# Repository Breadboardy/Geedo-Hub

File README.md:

# Geedo Hub

This is what every Geedo talks to. It serves animations and firmware updates
over the air, and it is where people share what they drew for him.

- **The Hub** — https://breadboardy.github.io/Geedo-Hub/
- **Draw one** — https://breadboardy.github.io/Geedo-Hub/make.html
- **Studio** — https://breadboardy.github.io/Geedo-Hub/studio/
- **Redeem a code** — https://breadboardy.github.io/Geedo-Hub/unlock.html

## How an animation gets on here

1. Draw it in the Studio and press **Publish**. That saves a `.geedo.json`
   and opens the [submission form](https://github.com/Breadboardy/Geedo-Hub/issues/new?template=publish-animation.yml).
2. The bot checks the file the way the robot would (size, speed, the flash
   rule) and posts a preview on the issue. Nothing is published yet.
3. A person looks at it. Every Geedo downloads everything on this list and
   most of the people watching those screens are kids, so nothing goes out
   unseen. A yes is the `approved` label; the bot packs it, lists it with the
   maker's name and the date, signs the manifest and pushes.
4. Every Geedo picks it up at its next check, within the minute.

The hardware design and firmware source are not public.

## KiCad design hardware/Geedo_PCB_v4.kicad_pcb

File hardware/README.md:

# Geedo PCB v4 — repaired (rev 4.3, single-side assembly + power sense)

## Rev 4.3: the board knows its own battery

Four 0402 parts on the back (machine side) give the firmware what rev 4.2
could not: battery voltage and charger status.

- **R10/R11 (100k/100k)**: divider from `/VBAT` to GND; midpoint
  `/VBAT_SENSE` goes to **IO0** (pad 12, ADC1_CH0). 4.2 V reads as 2.1 V,
  inside the ADC's range at 11 dB attenuation. Constant drain is 21 uA -
  about 2.7 years to self-drain a 500 mAh cell, negligible next to the ESP32.
- **C8 (100 nF)**: sampling/filter cap on the divider midpoint.
- **R9 (10k)**: series from the MCP73831's STAT pin (net now named
  `/STAT_RAW`) to **IO1** (pad 13) as `/CHG_STAT`. STAT is tri-state - LOW
  charging, HIGH done, Hi-Z unpowered - the series R prevents contention if
  the pin is ever misconfigured, and `INPUT_PULLUP` makes Hi-Z read HIGH.
- Deliberately NOT on IO2/IO8: those are boot-strapping pins and their
  pull-ups (R8/R2) are load-bearing. STAT driving one low at reset would
  stop the chip booting whenever USB was plugged in.

The schematic gained the same parts, IO0/IO1 pins on the ESP32C3 symbol, and
labels; sch<->pcb verified CONSISTENT. `fab/bom.csv` + `fab/cpl.csv` are
regenerated (19 line items, 29 placements; 100k = LCSC C25741). **If you
exported Gerbers before rev 4.3, re-export** - the old zip has no sense parts.

**Ground pads connect solid, not thermal.** The rev-4.3 sense routing
crowds the corridor under the module, and KiCad's DRC rightly complained
that several GND pads could only get one thermal spoke (it wants two).
Every SMD ground pad now uses a solid zone connection - electrically
better, standard on dense boards, and the parts are machine-reflowed so
the soldering argument for reliefs does not apply. The two through-hole
ground pins (J2/J3) keep their thermal reliefs because those are
hand-soldered.

Checker state after the change: clearance 0, edge 0, keepout 0, courtyards 0,
hole-to-hole 0, nets split 0, GND one pour, netlist CONSISTENT.

## Rev 4.2: one machine-assembled side

Rev 4.1 had SMD parts on both faces, which forces double-sided assembly -
two setups, two stencils, roughly double the labour charge. Rev 4.2 moves
every SMD part to the **back**, so the board qualifies for the cheap
single-side assembly tier:

- **Back (the machine side):** ESP32 module, USB-C, charger, regulator,
  BOOT + RESET buttons, LED, all passives - 22 parts, one paste-place-reflow
  pass. The USB port opens at the board edge as before, just on the back face.
- **Front (the human side):** only what the outside of Geedo touches - the
  OLED socket, the MAIN button, the battery connector, and the silkscreen
  face. All three parts are through-hole: they insert from the front and get
  soldered on the back, the classic TV-remote build. **Zero SMD passes on
  the front.**
- **SW1 stays the original SMD KSC6** (all three buttons are the same part,
  LCSC C221929). It is the one SMD part on the front, so the fab's
  single-side run does NOT place it - **you hand-solder SW1 yourself**: four
  big pads, an easy first SMD joint. For a production run, either pay for
  the second assembly side or swap SW1 to a 6x6 mm THT switch (that variant
  was built and verified in git history, commit c41971e).
- Everything re-routed from scratch (1000+ segments). The old CC2
  board-edge violations are gone - the new route no longer hugs the edge.
- `hardware/fab/bom.csv` and `hardware/fab/cpl.csv` are the assembly-house
  upload files. The LCSC numbers are suggestions - verify stock at order
  time, and expect the fab's reviewer to nudge some rotations; that is
  normal and they confirm before running.
- To revert the whole relayout:
  `cp hardware/Geedo_PCB_v4_BACKUP_two-sided.kicad_pcb hardware/Geedo_PCB_v4.kicad_pcb`

Verified: clearance 0, board-edge 0, keepout 0, courtyards 0, hole-to-hole 0,
all 17 nets single-piece, netlist 29/29 vs schematic, ground one pour with
every pad connected, and all 13 functional circuits (straps, EN reset, USB,
charger, LED, I2C) checked pad-by-pad. Run KiCad DRC with zones filled as the
final authority before ordering.

# Previous: rev 4.1 notes

The v4 design files had schematic symbols with **made-up pin numbers** that did not
match their real-world footprints, so the netlist landed on the wrong physical pads.
As uploaded, the board could not work at all. This revision repairs the netlists in
both the schematic and the board file. **It still needs re-routing in KiCad before
ordering** — see "What you still need to do" below.

## What was broken in v4

| # | Problem | Effect |
|---|---------|--------|
| 1 | Custom ESP32-C3 symbol numbered its pins 1–16 (including GPIOs IO12/IO13 that don't exist on a C3) while the footprint uses the real 53-pad module numbering | 3.3 V power landed on a GND pad, USB data on GND/IO1 pads, chip-enable (EN) on a no-connect pad — the module could never power up or boot |
| 2 | Custom USB-C symbol used pin numbers 1–6; the connector footprint's pads are named A1…B12/S1 | Zero matches → the USB connector was connected to **nothing** (no 5 V in, no data, no charging) |
| 3 | Custom MCP73831 charger symbol numbering wrong (real chip: STAT=1, VSS=2, VBAT=3, VDD=4, PROG=5) | 5 V was wired into the STAT status pin and the chip's actual power pin got the PROG resistor — charger dead |
| 4 | BOOT button on IO8 | ESP32-C3 download mode needs the button on **IO9** (IO8 must stay pulled high); a button on IO8 does nothing useful |
| 5 | IO2 strap pin floating | IO2 must be high at every boot and has no internal pull-up → unreliable/failed boots |
| 6 | Charge LED net floating; R7 shorted the STAT pin to GND | LED could never light |
| 7 | PROG resistor 1 k → commands ~1 A charge current | Double the MCP73831's 500 mA max — chip would overheat |

## What changed in rev 4.1

- `Geedo:ESP32C3` symbol renumbered to the real ESP32-C3-MINI-1 pad map
  (3V3→3, EN→8, IO3→6, IO4→18, IO5→19, IO8→22, USB D−→26/IO18, USB D+→27/IO19),
  plus proper GND pads (1, 2, 11, 14, 36–53, thermal 49_x) and new IO2/IO9 pins.
  Pin *positions* untouched, so the drawing and all existing wires are unchanged.
- `Geedo:USBC` symbol renumbered to real pads: VBUS=A4/B4/A9/B9, D+=A6/B6, D−=A7/B7,
  CC1=A5, CC2=B5, GND=A1/B1/A12/B12 + shield S1.
- `Geedo:MCP73831` renumbered to the real chip (STAT=1, VDD=4, PROG=5).
- Board pad nets rewritten to match all of the above (verified pad-by-pad).
- BOOT button moved to IO9 (`SW2`); the 10 k pull-up `R2` stays on IO8 as required.
- **New parts:** `R8` 10 k pull-up IO2→3V3 (required strap), `C5` 4.7 µF cap on VBUS
  at the charger input. Both are auto-placed — nudge them wherever you like.
- Charge LED rewired as a proper chain: 3V3 → D1 → R7 → STAT pin.
- `R6` (PROG) changed 1 k → **4.7 k** ≈ 215 mA charge current (safe for ≥350 mAh LiPo;
  use 10 k for ~100 mA if the battery is small).
- Removed 140 track segments/vias that were routed to the wrong physical pads.
  Power routing in the charger corner and the GND zones were kept.

## Routing status: bare board, ready to autoroute

All old copper was removed (it was routed to the wrong pads), so the board now has
footprints, nets, and GND zones but **zero tracks**. Net classes are preset so an
autorouter picks up sensible widths automatically:

| Class | Nets | Track width |
|-------|------|-------------|
| Power | GND, +3V3, /VBAT, /VBUS | 0.50 mm |
| USB | /USB_DP, /USB_DN | 0.30 mm |
| Default | everything else | 0.25 mm |

### Steps

Routing runs entirely from the terminal — no KiCad window needed:

```bash
./tools/route_pcb.sh          # export DSN -> Freerouting -> import SES -> save board
./tools/route_pcb.sh 500      # more optimisation passes
```

The script uses KiCad's own Python bindings (`ExportSpecctraDSN` /
`ImportSpecctraSES`, both headless-capable in KiCad 8+), so it needs the system
python that ships with KiCad — not a conda/venv python. It auto-skips any
Freerouting jar too new for the installed Java (2.2.x needs Java 25; the 1.9.0
build runs on Java 11+).

Afterwards:

1. **Check the USB pair by hand.** D+ and D− (J1 A6/B6 → U3 pad 27, A7/B7 → pad 26)
   should run short and side-by-side. If the autorouter sent them on separate
   scenic routes, delete those two tracks and drag them manually — the connector
   sits right next to the module, so it's a quick fix.
2. `kicad-cli pcb drc --schematic-parity hardware/Geedo_PCB_v4.kicad_pcb`
3. Open the board, press `B` to refill zones, and commit if DRC is clean.
4. **Schematic → ERC** once: one known warning, U1 pin "TEMP" has no pad — the
   5-pin MCP73831 has no TEMP pin; delete that symbol pin and its stub wire.

### Layout notes

- Front side: USB-C, ESP32 module, the three buttons, OLED header.
  Back side: charger, regulator, battery connector, all passives. Parts that look
  stacked in 2D (U1 under SW3, U2 under SW2) are on opposite faces — that's fine.
- `R8` sits at the top of the back-side pull-up column with R1/R2/R3;
  `C5` sits just below the charger U1. Both were auto-added in rev 4.1 — move them
  if you prefer, they have no mechanical constraint.

### Firmware pin map after this fix

MAIN button = GPIO3, BOOT/recovery = **GPIO9** (was 8 — update the sketch if it
read GPIO8), I2C `Wire.begin(4, 5)` (SDA=4, SCL=5). USB is native, no pin setup.
Flashing over USB now works normally; hold BOOT while pressing RESET only for recovery.

## Regulator: MCP1826S, not AMS1117 (changed in this revision)

`U2` was an AMS1117-3.3, which needs ~1.1 V more on its input than it puts out.
Fed from a LiPo that is the wrong way round:

| battery | AMS1117 output | MCP1826S output |
|---------|----------------|-----------------|
| 4.2 V (full) | 3.3 V | 3.3 V |
| 3.9 V (~70%) | ~3.2 V, sagging | 3.3 V |
| 3.7 V (nominal) | ~3.0 V, at the chip's minimum | 3.3 V |
| 3.5 V (~20%) | ~2.8 V, brownout | 3.3 V |

WiFi makes it worse exactly when it matters: an ESP32-C3 pulls 300-400 mA in
transmit bursts, which widens the dropout. The board would have run fine after
a charge and then reset during WiFi activity at half battery, losing most of
the pack's usable capacity.

The MCP1826S-3302 drops only 0.25 V, holds 3.3 V down to about 3.55 V of
battery, and keeps the same SOT-223 footprint. It is **not** pin-compatible -
AMS1117 is GND/Vout/Vin with the tab on Vout, MCP1826S is Vin/GND/Vout with the
tab on GND - so U2's pads were remapped and the three nets re-routed. The
schematic symbol was renumbered rather than redrawn, so the existing wiring is
unchanged. Tab-to-ground is also better thermally, since it bonds to the pour.

`C6` (1 uF, back side) was added as a local output capacitor for regulator
stability; C2's 10 uF is 9 mm away on the same net. It sits at (110.30, 115.80),
3 mm from U2's output pin, with 3.3 V routed to U2.3 in four segments that jog
around the VBAT via. It was originally placed 2 mm from the output pin on the
*wrong side* of it, which put it underneath U2's SOT-223 body - not assemblable,
and KiCad was right to flag the courtyard overlap.

`C7` (1 uF, back side, directly under the module's EN pad) was added between EN
and ground. Espressif's guidelines call for this RC with the 10 k pull-up: it
holds reset low while the rail rises, so the chip starts cleanly on a slow
power-up. Without it a board usually boots but can occasionally hang until
reset is pressed.

## Powering the board

The 3.3 V rail is generated from the **battery**. USB 5 V reaches only the
charger, so with no cell installed the MCP73831 has to act as the supply:
it is current-limited to 215 mA and can cycle when the load is light.

- **Flashing with a battery connected:** reliable. Native USB, no serial chip.
- **Flashing with no battery:** usually works (download mode draws well under
  the limit) but the rail is unregulated-ish and a brownout mid-write is
  possible. Nothing is damaged; just retry.
- **Running WiFi with no battery:** will brown out on transmit bursts.

Feeding the regulator from USB *or* battery would fix this properly and is the
main remaining item for rev 5.

## Ground plane: SW2's ground was floating

The copper pour on the front side is split by the CC2 track that runs down
the right-hand side of the board. The strip east of it (roughly x 114-118.5,
y 105-126) carries **SW2's two ground pads** and had no via anywhere on it,
so the BOOT button's ground return was connected to nothing. Two stitching
vias at (118.0, 120.9) and (118.0, 117.4) tie that strip down to the back-side
plane. Ground now resolves to a single 2042 mm2 piece across both layers.

This is what the long-standing "Zone [GND] on F.Cu / Zone [GND] on B.Cu -
unconnected" DRC item was pointing at. It went unexplained for a while because
the offline checking scripts modelled SW2's pads with their width and height
swapped, which painted false copper straight across the gap.

## The antenna keepout was thrown off the board by the flip

Spotted by eye in KiCad: the ESP32's antenna keepout rectangle was drawn far
off to the left of the board, nowhere near the module.

`ESP32-C3-MINI-1` carries three keepout zones nested inside its footprint,
covering the antenna end of the module. **Zones nested in a footprint store
absolute board coordinates**, unlike pads, lines and polygons, which are
footprint-local. The rev-4.2 flip negated every local x, so it turned the
keepout's `x 90.575..103.775` into `-103.775..-90.575` — mirrored about x=0
instead of about the footprint origin, landing ~190 mm off the board.

Nothing flagged it. KiCad's DRC has no rule for "antenna is missing its
keepout", and the board is saved unfilled, so the damage only appears at
**Edit → Fill Zones** — the step right before Gerber export. Simulating the
pour on the pre-fix file shows the ground plane flooding the antenna window
almost completely: 71.2 mm2 on F.Cu and 70.5 mm2 on B.Cu, out of 71.3 mm2.
Solid copper on both sides of a printed antenna detunes it and shorts out its
near field, so the radio would have been crippled on every board in the order.

The fix restores `x 90.575..103.775`. The rectangle is centred on U3's origin
(x = 97.175), so mirroring maps it onto itself — a flipped module needs the
exact same absolute keepout as an unflipped one. After the fix the pour is
kept out entirely (0.65 mm2 residual per layer, which is one 0.05 mm grid row
at the window edge — a rasteriser artifact, not copper).

`tools/flip_footprint.py` carried the same latent bug and would have repeated
it on any future flip. It now holds nested zones out of the local-coordinate
rewrite and mirrors them about the footprint origin with exact decimal
arithmetic, guarded by a new self-test **T5** (zone vertices must land at
`2*fx - x`, alongside T2 for pads). Cross-check: re-flipping U3 from the
two-sided backup with the repaired tool reproduces the corrected coordinates
exactly.

## The 3.3 V rail was in two halves

Caught by KiCad's DRC, not by me. `+3V3` was split into two electrically
separate islands with nothing joining them:

| island | what was on it |
|--------|----------------|
| A | U3.3 (ESP32 3.3 V), U2.3 (regulator output), C6.1, D1.2 |
| B | **J3.2 (OLED 3.3 V)**, R1.1, R2.1, R3.1, R8.1, C2.1, C3.1, C4.1 |

So the regulator's output never reached the OLED header or **any** of the
pull-ups - including the IO2 and IO8 strapping resistors the ESP32-C3 needs
held high to boot, and the IO9 pull-up. The board would not have started.

The routing had got within 1.2 mm of finishing and stopped: a front-side stub
dead-ended at (103.15, 77.85) and a back-side track dead-ended at
(103.96, 77.00), on opposite layers with no via between them. Fixed with a via
at the front-side tip and a 0.5 mm back-side track joining the two.

KiCad reported this as a single "unconnected items" entry, which badly
undersells it - one missing connection was the whole upper half of the rail.
Every net is now checked island-by-island, not just pad-to-pad; see
`tools/drc_offline.py`.

## The logo, and why it never printed

The face logo was a KiCad **reference image** - an `(image ...)` element with a
1254x1254 PNG embedded as base64. Reference images are editor-only: they exist
to trace over and line things up, and KiCad **never plots them to Gerbers**. The
fab had never seen it, on any board.

It was also far too small to print. The PNG is 96% whitespace padding, so at the
stored scale the actual face came out 2.3 mm wide with 0.18 mm strokes - right at
the silkscreen minimum, patchy at best even if it had plotted.

It is now real artwork: the bitmap is traced into outlines and stored as a
footprint, `Geedo:Logo`, of `fp_poly` shapes on **F.SilkS**, which does plot.
Sits at (115.5, 77.5), sized so the face is 6 mm wide with 0.47 mm strokes,
0.90 mm inside the top edge and 1.16 mm from the nearest pad. The mouth's enclosed hole is preserved by fracturing - the hole
is joined to its outer contour by a zero-width slit, which is exactly what
KiCad's own bitmap converter does.

The reference image was removed: it plotted nothing, it sat directly on top of
the new artwork in the editor, and it was 912 kB of base64 in a 1.1 MB board
file (now 205 kB). The source bitmap is kept as `hardware/geedo-logo.png`.

To move or resize it, drag the `LOGO1` footprint in KiCad like any other. To put
it in **copper** instead of silkscreen - bare copper reads gold on ENIG and looks
sharper than white ink - change the `fp_poly` layers to `F.Cu`; it would then
need clearance from the ground pour, so re-run `tools/drc_offline.py` after.

The `Geedo` copper text on the back has been **deleted**. It had been moved once,
from (118.5, 81) to (112.55, 87.3), because a 3.3 V track ran straight through the
lettering - KiCad flagged that as a 0.000 mm clearance violation - but the board
carries its name in the silkscreen logo now, so the copper lettering is gone. That
also means there is no unconnected copper island sitting in the ground pour.

## Check your OLED module's pin order before plugging it in

The header `J3` is wired, physically, as:

| pin | net |
|-----|-----|
| 1 (square pad) | GND |
| 2 | 3V3 |
| 3 | SCL |
| 4 | SDA |

**Checked: the module in use is GND-first, so it matches and plugs straight in.**

Worth knowing if you ever swap displays: some SSD1306 breakouts are ordered
VCC, GND, SCL, SDA instead. Plugging one of those straight in puts 3.3 V on its
ground pin and ground on its supply, which destroys it. Compare the silkscreen
on any new module against the table above first; if it does not match, swap the
two power wires. The board is not wrong, both module variants simply exist.

The schematic used to disagree with this. Its `Conn4` symbol named the pins
VCC, GND, SDA, SCL - both pairs the wrong way round from how the wires actually
run. The wiring and the board were always self-consistent; only the names on the
symbol were wrong, so anyone reading the schematic would have got it backwards.
The pin names now match reality.

Ten other pin labels were stale in the same way, left behind when the symbols
were renumbered. `U2` was still carrying **AMS1117** pin names (`VI`, `VO`,
`GND_Adj`) although it is an MCP1826S, and `U1`'s labels were one position out.
All nets were correct throughout - these were names only - but they are now
corrected so the board reads truthfully in KiCad.

## Not done, if you want them later

- **No reference designators are printed.** 25 of the 26 are hidden, so the
  board gets component outlines and polarity marks but no `R1`/`C2`/`U3` text.
  With four different values across eight identical-looking 0402 resistors,
  hand-populating this means counting positions off the layout. Un-hiding them
  is possible but not automatic: several sit 15-36 mm from their own part, so
  they would need repositioning, and four would land on pads.
- **No pull-ups on SDA/SCL.** I2C needs them. Most SSD1306 modules have their
  own on board, in which case this is fine; if yours does not, the bus will not
  work at all. Two 0402 resistors, 4.7 k, from SDA and SCL to 3V3 would settle it.

## Remaining DRC items

After the last pass KiCad reports **0 unconnected pads**. What is left:

| item | severity | why it stays |
|------|----------|--------------|
| 3x `copper_edge_clearance` on the CC2 trace, 0.348 mm vs 0.5 mm | error | Genuinely unfixable in this layout - see the rev 5 note below. Fabs build 0.35 mm to the outline routinely. |
| `lib_footprint_mismatch` on U3 | warning | The ESP32 module footprint is custom and edited, so it will always differ from the library copy. No effect on fabrication. |

The logo footprint lives in `hardware/Geedo.pretty/`, registered by
`hardware/fp-lib-table`, so `Geedo:Logo` resolves instead of reporting a
missing library.

C5 and C7 previously reported `lib_footprint_mismatch` too. They sat at
rotation 0 while their pads carried an absolute angle of 180, which KiCad reads
as differing from the library. The pads are symmetric roundrects so the two are
the same shape - normalising the angle is bookkeeping, not a geometry change.

## Checking the board without opening KiCad

Two scripts check the board straight from the `.kicad_pcb` file, so they work
on a machine with no KiCad installed and they do not care whether the zones
happen to be filled. Run both from the repo root:

```bash
python3 tools/drc_offline.py    # clearance, board edge, keepout
python3 tools/pour_sim.py       # re-derives the pour, checks GND is one net
```

`pour_sim.py` needs numpy and scipy. It does not read the stored
`filled_polygon` blocks - those go stale the moment anything is re-routed.
It rebuilds the fill from the zone rules instead (clearance, min thickness,
keepouts, edge clearance, island removal), then merges the two layers at
through-hole pads and vias and flood-fills. That is what caught SW2's
floating ground island.

Expected output as of this revision: 0 clearance, 0 keepout, 4 board-edge
(the CC2 trace described below), and ground resolving to a single group with
every ground pad on poured copper. Courtyard overlaps: 0. Nets split across
islands: 0.

These are a second opinion, not a replacement for KiCad's DRC - they do not
model solder-mask bridging, starved thermals or footprint-library parity.
Run `kicad-cli pcb drc --schematic-parity hardware/Geedo_PCB_v4.kicad_pcb`
before ordering, with the zones filled.

## Known caveats to fix in rev 5

- No ESD protection on the USB data lines (add a USBLC6-2SC6 next to J1).
- The CC2 trace runs 0.35 mm from the bottom board edge where the setup asks
  0.5 mm. This one cannot be fixed by moving the trace: it threads the gap
  between SW2's lower pad and the board outline, which is 0.8 mm wide, and
  clearing the pad by 0.2 mm plus the edge by 0.5 mm needs 0.95 mm. Lifting it
  just trades an edge violation for a 0.025 mm pad clearance, which is far
  worse. Fixing it properly means nudging SW2 up a millimetre in rev 5. Most
  fabs build 0.35 mm to the outline without comment.

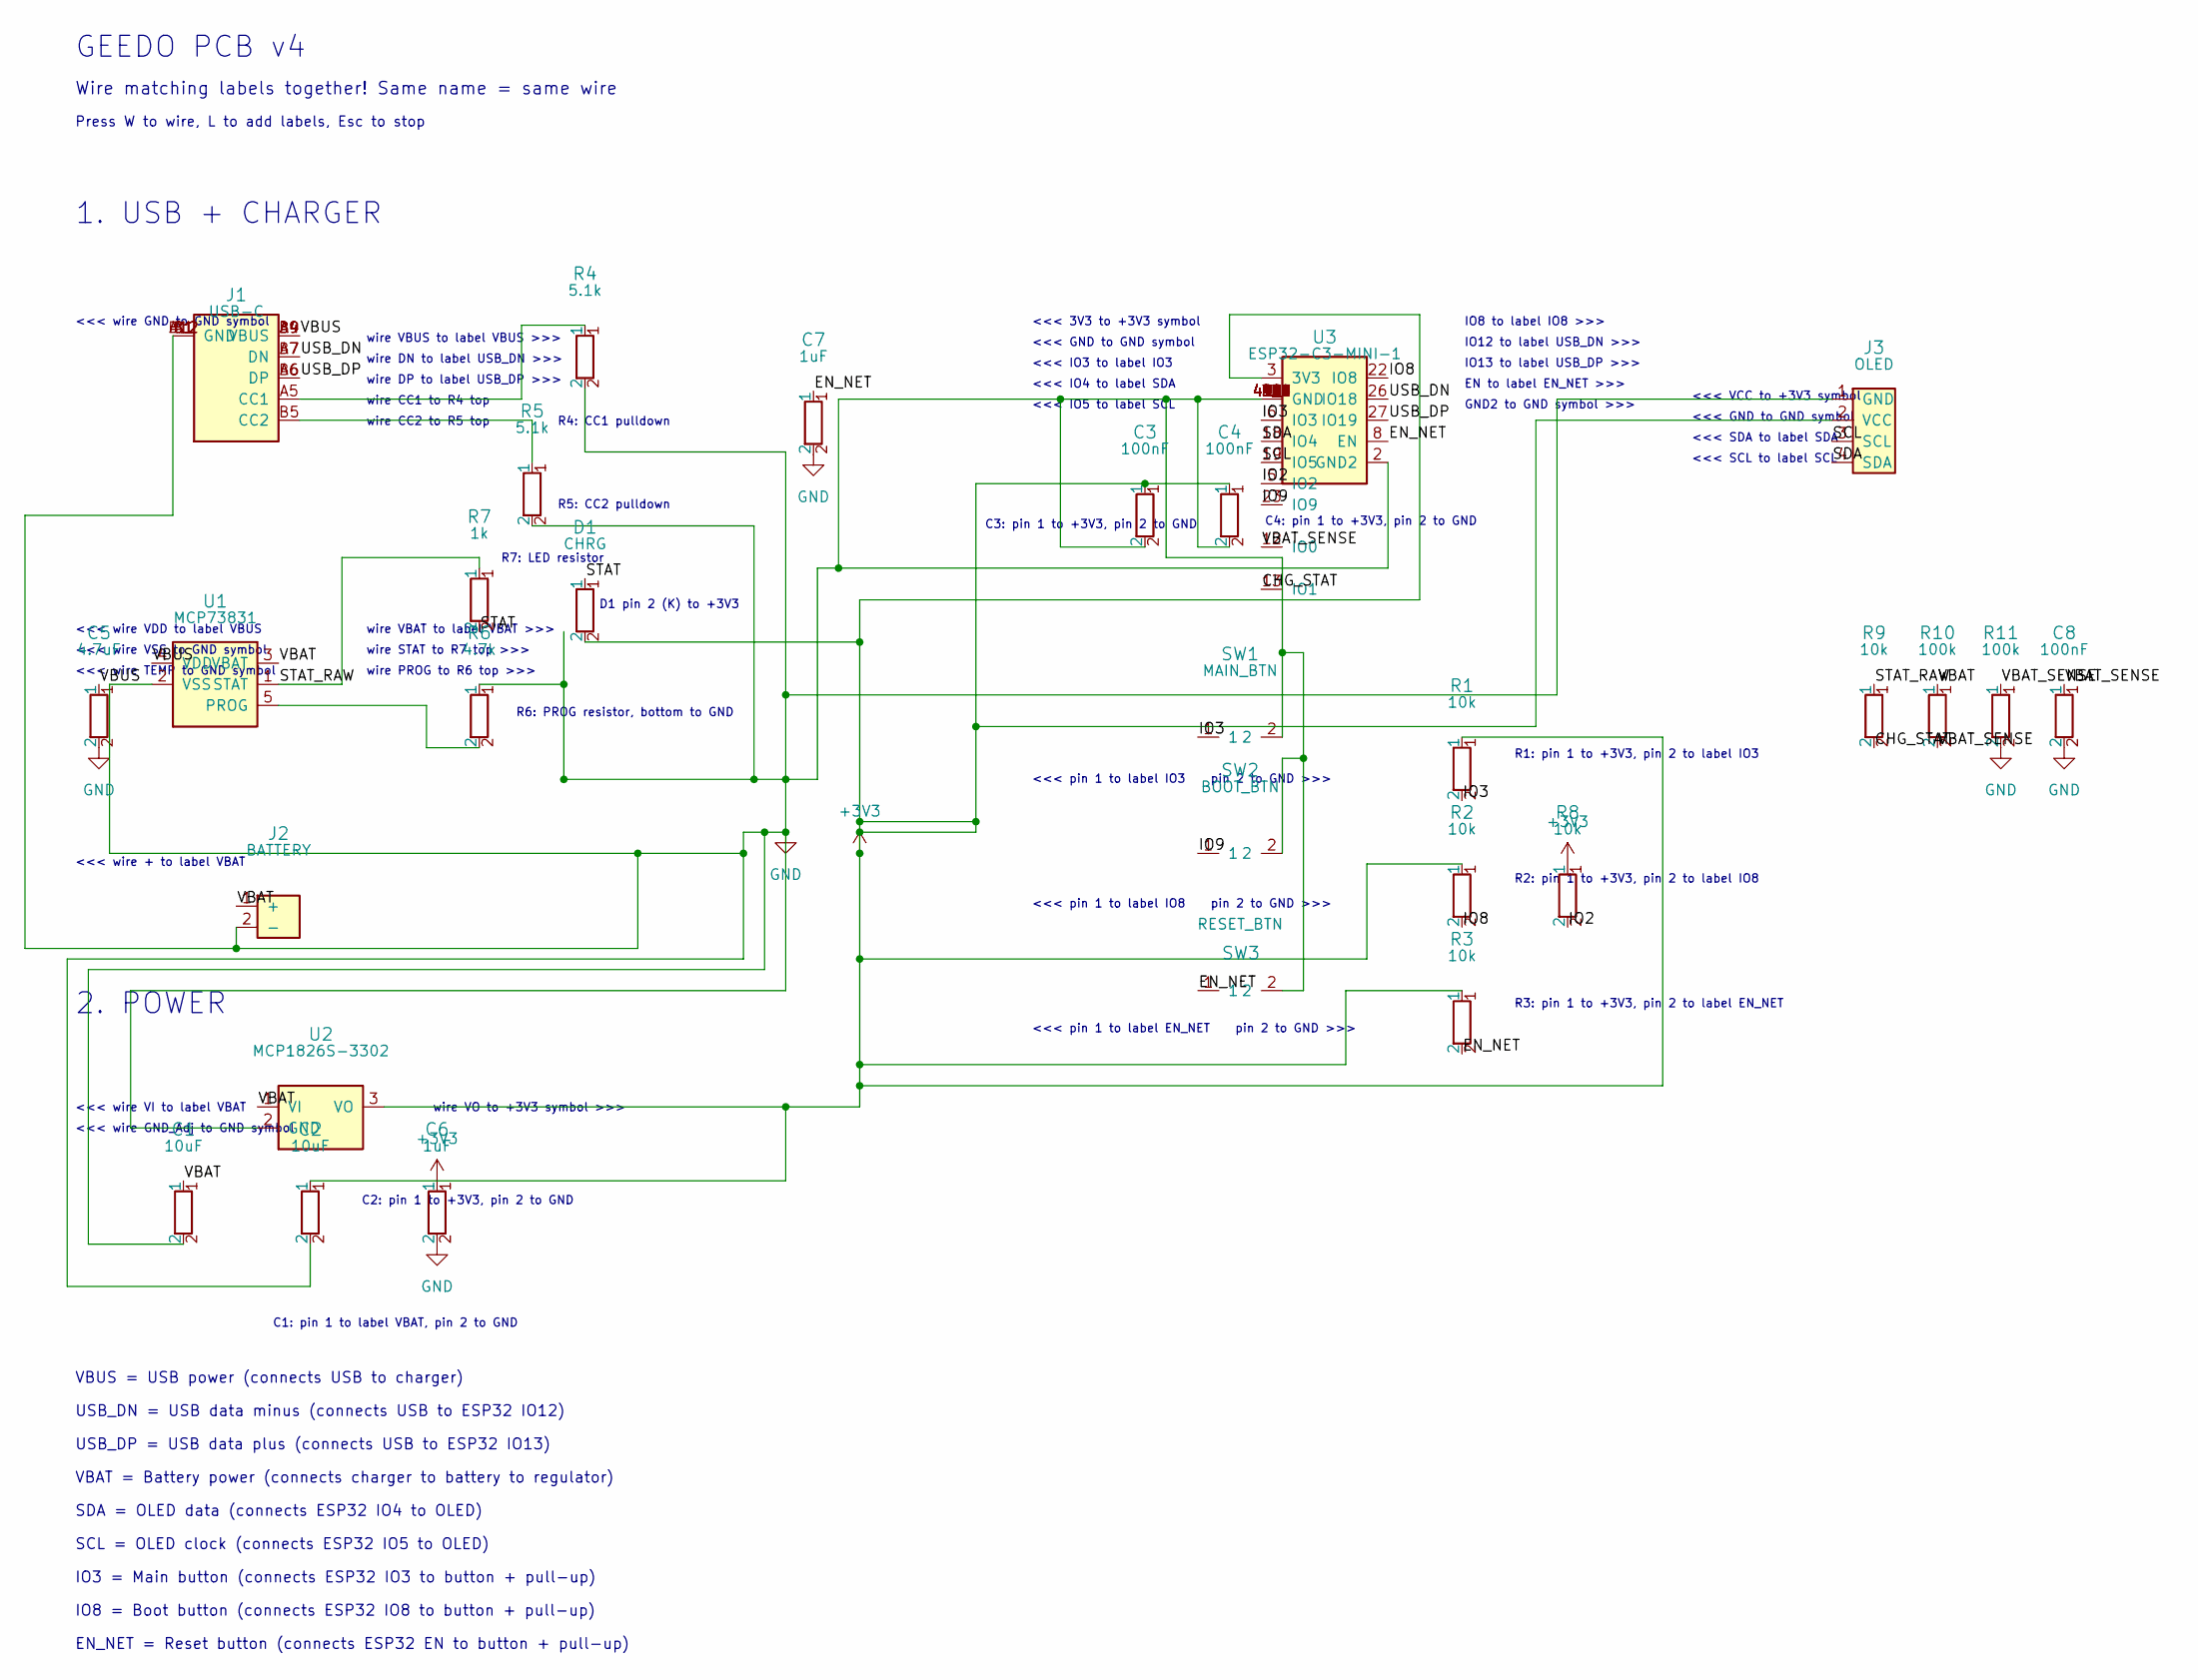
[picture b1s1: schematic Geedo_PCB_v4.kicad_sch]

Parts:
C1, C2: 10uF; C_0402_1005Metric
C3, C4, C8: 100nF; C_0402_1005Metric
C5: 4.7uF; C_0402_1005Metric
C6, C7: 1uF; C_0402_1005Metric
D1: CHRG; LED_0402_1005Metric
J1: USB-C; USB_C_Receptacle_HRO_TYPE-C-31-M-12
J2: BATTERY; JST_PH_B2B-PH-K_1x02_P2.00mm_Vertical
J3: OLED; PinSocket_1x04_P2.54mm_Vertical
R1, R2, R3, R8, R9: 10k; R_0402_1005Metric
R4, R5: 5.1k; R_0402_1005Metric
R6: 4.7k; R_0402_1005Metric
R7: 1k; R_0402_1005Metric
R10, R11: 100k; R_0402_1005Metric
SW1: MAIN_BTN; SW_Push_1P1T_NO_CK_KSC6xxJ
SW2: BOOT_BTN; SW_Push_1P1T_NO_CK_KSC6xxJ
SW3: RESET_BTN; SW_Push_1P1T_NO_CK_KSC6xxJ
U1: MCP73831; SOT-23-5
U2: MCP1826S-3302; SOT-223-3_TabPin2
U3: ESP32-C3-MINI-1; XCVR_ESP32-C3-MINI-1-N4

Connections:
+3V3: C2.1, C3.1, C4.1, C6.1, D1.2, J3.2 (VCC), R1.1, R2.1, R3.1, R8.1, U2.3 (VOUT), U3.3 (3V3)
/CHG_STAT: R9.2, U3.13 (IO12)
/EN_NET: C7.1, R3.2, SW3.1, U3.8 (EN)
/IO2: R8.2, U3.5 (IO4)
/IO3: R1.2, SW1.1, U3.6 (IO5)
/IO8: R2.2, U3.22 (IO8)
/IO9: SW2.1, U3.23 (IO9)
/SCL: J3.3 (SCL), U3.19 (IO5)
/SDA: J3.4 (SDA), U3.18 (IO4)
/STAT: D1.1, R7.2
/STAT_RAW: R7.1, R9.1, U1.1 (STAT)
/USB_DN: J1.A7 (DN), J1.B7 (DN), U3.26 (IO18)
/USB_DP: J1.A6 (DP), J1.B6 (DP), U3.27 (IO19)
/VBAT: C1.1, J2.1 (+), R10.1, U1.3 (VBAT), U2.1 (VIN)
/VBAT_SENSE: C8.1, R10.2, R11.1, U3.12 (IO0)
/VBUS: C5.1, J1.A4 (VBUS), J1.A9 (VBUS), J1.B4 (VBUS), J1.B9 (VBUS), U1.4 (VDD)
GND: C1.2, C2.2, C3.2, C4.2, C5.2, C6.2, C7.2, C8.2, J1.A1 (GND), J1.A12 (GND), J1.B1 (GND), J1.B12 (GND), J1.S1 (GND), J2.2 (-), J3.1 (GND), R4.2, R5.2, R6.1, R11.2, SW1.2, SW2.2, SW3.2, U1.2 (VSS), U2.2 (GND), U3.1 (GND), U3.2 (3V3), U3.11 (GND), U3.14 (IO13), U3.36 (GND), U3.37 (GND), U3.38 (GND), U3.39 (GND), U3.40 (GND), U3.41 (GND), U3.42 (GND), U3.43 (GND), U3.44 (GND), U3.45 (GND), U3.46 (GND), U3.47 (GND), U3.48 (GND), U3.49_1 (GND), U3.49_2 (GND), U3.49_3 (GND), U3.49_4 (GND), U3.49_5 (GND), U3.49_6 (GND), U3.49_7 (GND), U3.49_8 (GND), U3.49_9 (GND), U3.50 (GND), U3.51 (GND), U3.52 (GND), U3.53 (GND)
unnamed: J1.A5 (CC1), R4.1
unnamed: J1.B5 (CC2), R5.1
unnamed: R6.2, U1.5 (PROG)

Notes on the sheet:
C4: pin 1 to +3V3, pin 2 to GND
wire DP to label USB_DP >>>
wire DN to label USB_DN >>>
<<< wire TEMP to GND symbol
EN_NET = Reset button (connects ESP32 EN to button + pull-up)
<<< pin 1 to label EN_NET pin 2 to GND >>>
VBUS = USB power (connects USB to charger)
IO8 to label IO8 >>>
R2: pin 1 to +3V3, pin 2 to label IO8
<<< wire VDD to label VBUS
<<< GND to GND symbol
R7: LED resistor
Press W to wire, L to add labels, Esc to stop
<<< IO5 to label SCL
wire CC1 to R4 top
C3: pin 1 to +3V3, pin 2 to GND
VBAT = Battery power (connects charger to battery to regulator)
2. POWER
<<< SCL to label SCL
<<< IO3 to label IO3
R6: PROG resistor, bottom to GND
EN to label EN_NET >>>
IO8 = Boot button (connects ESP32 IO8 to button + pull-up)
R5: CC2 pulldown
R3: pin 1 to +3V3, pin 2 to label EN_NET
IO3 = Main button (connects ESP32 IO3 to button + pull-up)
<<< wire VI to label VBAT
<<< SDA to label SDA
<<< IO4 to label SDA
<<< wire GND to GND symbol
IO13 to label USB_DP >>>
GND2 to GND symbol >>>
SCL = OLED clock (connects ESP32 IO5 to OLED)
wire VO to +3V3 symbol >>>
Wire matching labels together! Same name = same wire
wire VBAT to label VBAT >>>
<<< wire GND_Adj to GND symbol
<<< wire + to label VBAT
wire STAT to R7 top >>>
D1 pin 2 (K) to +3V3

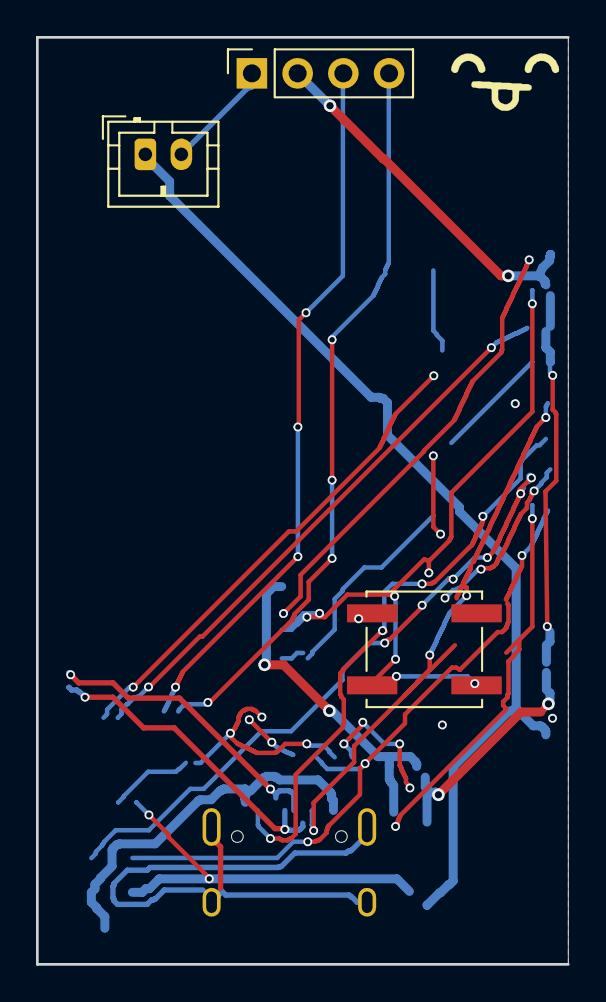
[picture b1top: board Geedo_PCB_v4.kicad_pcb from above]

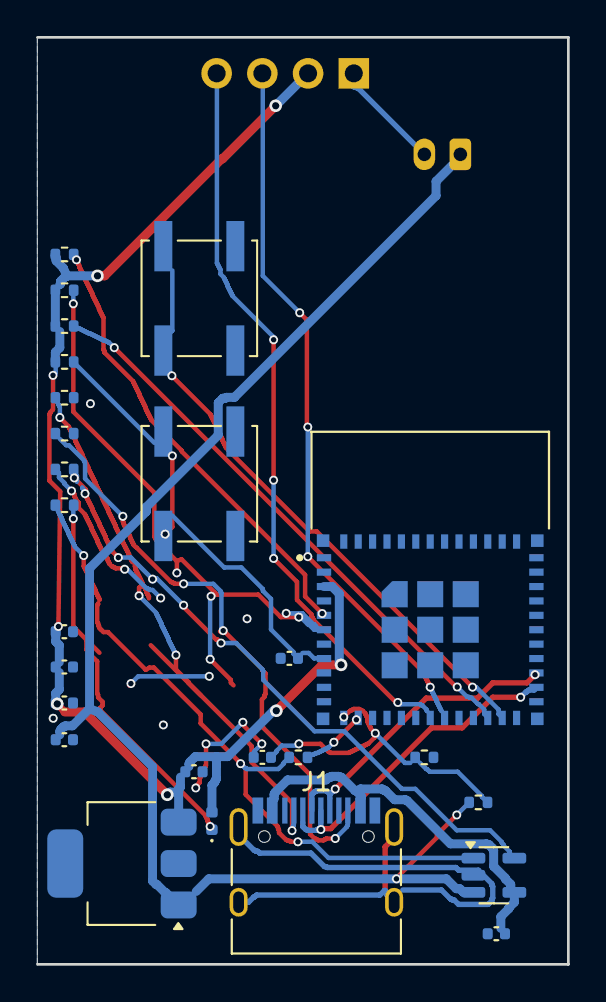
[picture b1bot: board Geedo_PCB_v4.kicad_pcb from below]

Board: 2 copper layers, 29.5 x 51.5 mm, 30 parts (26 on the bottom side), 20 nets.

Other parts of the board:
LOGO1: Geedo; Logo

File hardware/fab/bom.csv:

Comment,Designator,Footprint,LCSC Part #
100k,"R10,R11",R_0402_1005Metric,C25741
100nF,"C3,C4,C8",C_0402_1005Metric,C1525
10k,"R1,R2,R3,R8,R9",R_0402_1005Metric,C25744
10uF,"C1,C2",C_0402_1005Metric,C15525
1k,R7,R_0402_1005Metric,C11702
1uF,"C6,C7",C_0402_1005Metric,C52923
4.7k,R6,R_0402_1005Metric,C25900
4.7uF,C5,C_0402_1005Metric,C23733
5.1k,"R4,R5",R_0402_1005Metric,C25905
BATTERY,J2,JST_PH_B2B-PH-K_1x02_P2.00mm_Vertical,C131337
BOOT_BTN,SW2,SW_Push_1P1T_NO_CK_KSC6xxJ,C221929
CHRG,D1,LED_0402_1005Metric,C2286
ESP32-C3-MINI-1,U3,XCVR_ESP32-C3-MINI-1-N4,C3013922
MAIN_BTN,SW1,SW_Push_1P1T_NO_CK_KSC6xxJ,C221929
MCP1826S-3302,U2,SOT-223-3_TabPin2,C39041
MCP73831,U1,SOT-23-5,C424093
OLED,J3,PinSocket_1x04_P2.54mm_Vertical,C2718436
RESET_BTN,SW3,SW_Push_1P1T_NO_CK_KSC6xxJ,C221929
USB-C,J1,USB_C_Receptacle_HRO_TYPE-C-31-M-12,C165948

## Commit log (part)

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2026-05-19 Initial Geedo Hub
2026-05-19 Add OTA firmware support
2026-05-19 firmware v2
2026-05-19 Add hub landing page with animation grid + firmware card
2026-05-19 firmware v3
2026-05-19 firmware v4
2026-05-19 firmware v5
2026-05-19 firmware v7
2026-05-19 add eating animations (9 food items)
2026-05-19 firmware v8
2026-05-19 hub: hover-to-play, likes & stars (localStorage)
2026-05-19 ci: auto-publish animations from labeled issues
2026-05-19 hub: NEW + POPULAR sections; allow non-maintainer publishing with user_ namespace
2026-05-19 hub: lazy-load, filter tabs (Community/Official/categories), search, pagination
2026-05-22 firmware v11
